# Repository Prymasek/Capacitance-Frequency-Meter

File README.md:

<div align="center">

# 🔬 ESP32-C3-Zero Capacitance & Frequency Meter

### Compact open-source capacitance and frequency meter

### Kompaktowy miernik pojemności i częstotliwości

<br>

🇵🇱 **Polski** | 🇬🇧 **English**

<br>

</div>

---

# 🇵🇱 Polski

## 📖 Opis projektu

**ESP32-C3-Zero Capacitance & Frequency Meter** to kompaktowy, otwartoźródłowy miernik pojemności oraz częstotliwości oparty na mikrokontrolerze **ESP32-C3-Zero**.

Projekt został stworzony jako niedrogie i praktyczne narzędzie pomiarowe do pracy z elektroniką. Urządzenie pozwala mierzyć pojemność kondensatorów od około **33 pF** oraz częstotliwość sygnałów cyfrowych do **250 kHz**.

Repozytorium zawiera zarówno część programową, jak i sprzętową projektu: firmware, schemat oraz projekt PCB wykonany w **KiCad 9.0**.

---

## 📸 Zdjęcia projektu

<div align="center">

### Gotowe urządzenie

<br><br>

### Spód płytki PCB

<br><br>

### Wizualizacja 3D PCB

</div>

---

## ✨ Najważniejsze funkcje

* ⚡ Pomiar pojemności kondensatorów
* 📡 Pomiar częstotliwości sygnałów
* 🔁 Automatyczny dobór zakresu pomiarowego
* 🎯 Funkcja TARE do kompensacji pojemności pasożytniczej
* ⏸️ Funkcja zatrzymania pomiaru częstotliwości
* 🧩 Projekt PCB wykonany w KiCad 9.0
* 🔓 Otwarty kod źródłowy
* 🛠️ Możliwość dalszej rozbudowy projektu

---

## ⚙️ Zasada działania

### ⚡ Pomiar pojemności

Pomiar pojemności realizowany jest poprzez pomiar czasu ładowania kondensatora przez rezystor o znanej wartości.

Mikrokontroler **ESP32-C3-Zero** mierzy czas potrzebny do osiągnięcia określonego progu napięcia wykrywanego przez szybki komparator **LT1016**.

W projekcie zastosowano dwa zakresy pomiarowe:

| Zakres          | Rezystor |
| --------------- | -------- |
| Małe pojemności | 100 kΩ   |
| Duże pojemności | 2.2 kΩ   |

Przełączanie zakresu odbywa się automatycznie w programie.

---

### 📡 Pomiar częstotliwości

Sygnał wejściowy podawany jest bezpośrednio na wejście mikrokontrolera ESP32-C3.

Każde narastające zbocze sygnału wywołuje przerwanie sprzętowe. Program zlicza impulsy w określonym czasie, a następnie przelicza wynik na częstotliwość.

Obsługiwane jednostki:

* Hz
* kHz
* MHz

---

## 🔧 Wykorzystane elementy

| Element         | Opis                       |
| --------------- | -------------------------- |
| ESP32-C3-Zero   | Główny mikrokontroler      |
| LT1016          | Szybki komparator napięcia |
| Rezystor 100 kΩ | Zakres małych pojemności   |
| Rezystor 2.2 kΩ | Zakres dużych pojemności   |
| Przyciski TACT  | Sterowanie urządzeniem     |
| Złącza goldpin  | Wejścia pomiarowe          |

---

## 📦 Zawartość repozytorium

Repozytorium zawiera:

* 📄 Firmware dla ESP32-C3-Zero
* 🧩 Schemat elektryczny KiCad 9.0
* 🧩 Projekt PCB KiCad 9.0
* 📷 Zdjęcia gotowego urządzenia
* 📘 Dokumentację projektu

---

## 📂 Struktura projektu

```text
.
├── firmware/
│   └── cap&frq_meter.ino
│
├── hardware/
│   ├── cap&frq_meter.kicad_sch
│   └── cap&frq_meter.kicad_pcb
│
├── images/
│
├── README.md
└── LICENSE
```

---

## 🛠️ Oprogramowanie

Firmware został napisany w języku **C++** z wykorzystaniem środowiska **Arduino IDE** oraz rdzenia **Arduino Core for ESP32**.

Wykorzystane biblioteki:

* Arduino Core for ESP32
* LiquidCrystal

---

## 🚀 Możliwe rozszerzenia

* Pomiar ESR kondensatorów
* Pomiar rezystancji
* Pomiar indukcyjności
* Wyświetlacz OLED/TFT
* Zasilanie akumulatorowe
* Automatyczna kalibracja
* Rozszerzenie zakresów pomiarowych

---

<br>

<div align="center">

# 🇬🇧 English

</div>

---

## 📖 Project Description

**ESP32-C3-Zero Capacitance & Frequency Meter** is a compact open-source capacitance and frequency meter based on the **ESP32-C3-Zero** microcontroller.

The project was created as a low-cost and practical measurement tool for electronics work. The device can measure capacitor values starting from approximately **33 pF** and digital signal frequencies up to **250 kHz**.

This repository contains both the software and hardware parts of the project: firmware, schematic and PCB design created in **KiCad 9.0**.

---

## 📸 Project Gallery

<div align="center">

### Finished Device

<br><br>

### PCB Bottom Layer

<br><br>

### 3D PCB View

</div>

---

## ✨ Key Features

* ⚡ Capacitance measurement
* 📡 Frequency measurement
* 🔁 Automatic measurement range selection
* 🎯 TARE compensation for parasitic capacitance
* ⏸️ Frequency measurement hold function
* 🧩 PCB design created in KiCad 9.0
* 🔓 Open-source firmware
* 🛠️ Easy to modify and expand

---

## ⚙️ Operating Principle

### ⚡ Capacitance Measurement

Capacitance is measured by monitoring the charging time of a capacitor through a resistor with a known value.

The **ESP32-C3-Zero** measures the time required to reach a voltage threshold detected by the high-speed **LT1016** comparator.

Two measurement ranges are used:

| Range              | Resistor |
| ------------------ | -------- |
| Small capacitances | 100 kΩ   |
| Large capacitances | 2.2 kΩ   |

Range switching is performed automatically in firmware.

---

### 📡 Frequency Measurement

The input signal is connected directly to an ESP32-C3 input pin.

Each rising edge of the signal generates a hardware interrupt. The firmware counts pulses over a defined time period and converts the result into frequency.

Supported units:

* Hz
* kHz
* MHz

---

## 🔧 Hardware Components

| Component       | Description                   |
| --------------- | ----------------------------- |
| ESP32-C3-Zero   | Main microcontroller          |
| LT1016          | High-speed voltage comparator |
| 100 kΩ resistor | Small capacitance range       |
| 2.2 kΩ resistor | Large capacitance range       |
| TACT switches   | User controls                 |
| Pin headers     | Measurement inputs            |

---

## 📦 Repository Contents

This repository contains:

* 📄 Firmware for ESP32-C3-Zero
* 🧩 KiCad 9.0 schematic file
* 🧩 KiCad 9.0 PCB file
* 📷 Photos of the assembled device
* 📘 Project documentation

---

## 📂 Project Structure

```text
.
├── firmware/
│   └── cap&frq_meter.ino
│
├── hardware/
│   ├── cap&frq_meter.kicad_sch
│   └── cap&frq_meter.kicad_pcb
│
├── images/
│
├── README.md
└── LICENSE
```

---

## 🛠️ Software

The firmware is written in **C++** using **Arduino IDE** and **Arduino Core for ESP32**.

Libraries used:

* Arduino Core for ESP32
* LiquidCrystal

---

## 🚀 Future Improvements

* ESR measurement
* Resistance measurement
* Inductance measurement
* OLED/TFT display support
* Battery-powered version
* Automatic calibration
* Extended measurement ranges

---

## 📄 License

Released under the MIT License.

Feel free to use, modify and improve the project.

---

<div align="center">

### ⭐ If you like this project, consider leaving a star on GitHub.

</div>

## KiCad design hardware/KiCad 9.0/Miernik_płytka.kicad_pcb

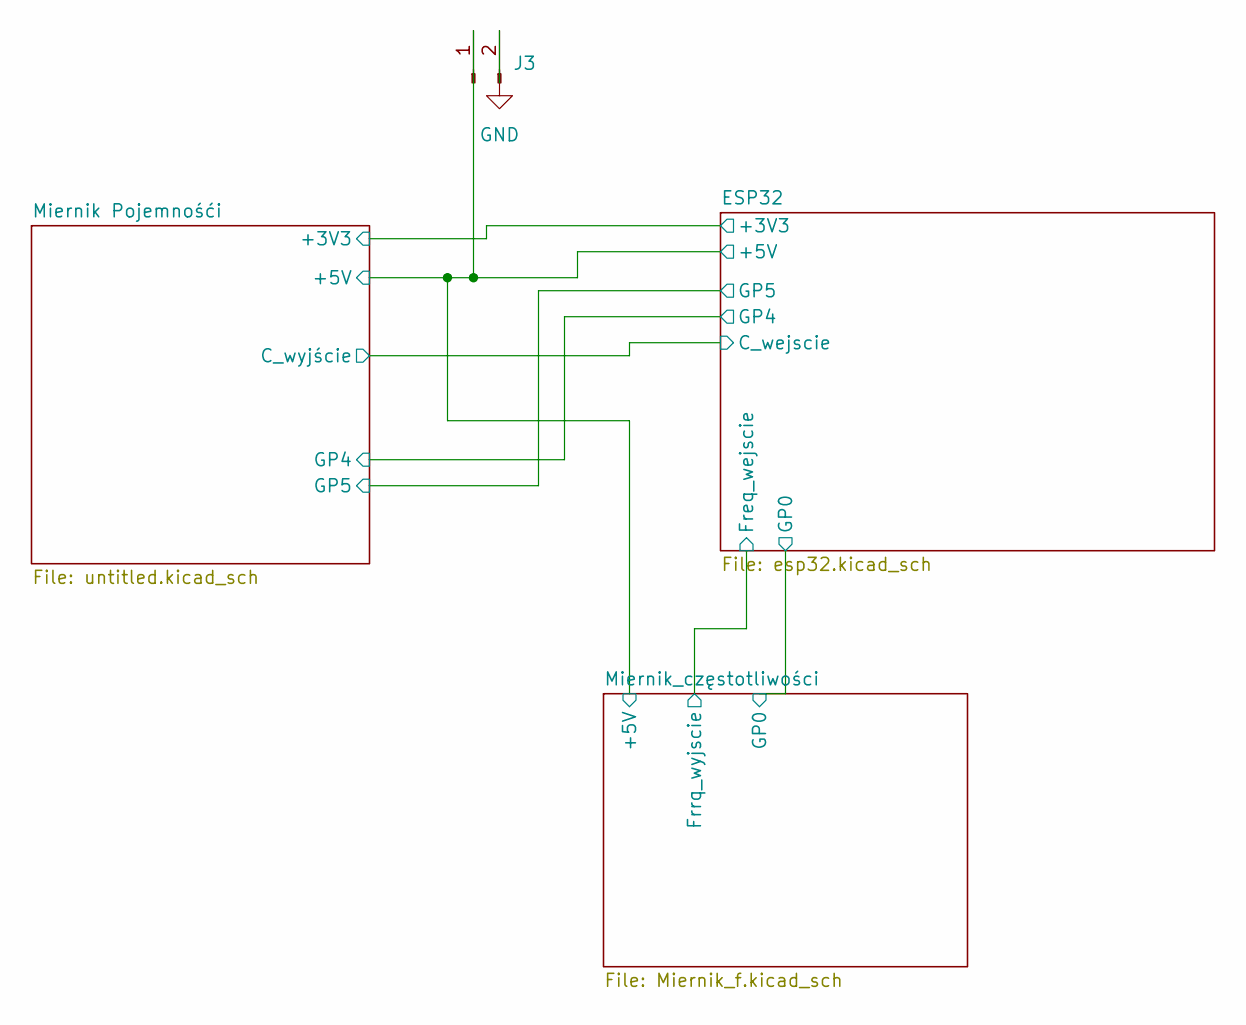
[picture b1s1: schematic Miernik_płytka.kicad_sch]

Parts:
J3: Conn_01x02_Pin; PinSocket_1x02_P2.54mm_Vertical

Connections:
/ESP32/+5V: J3.1; also elsewhere on the board
GND: J3.2; also elsewhere on the board

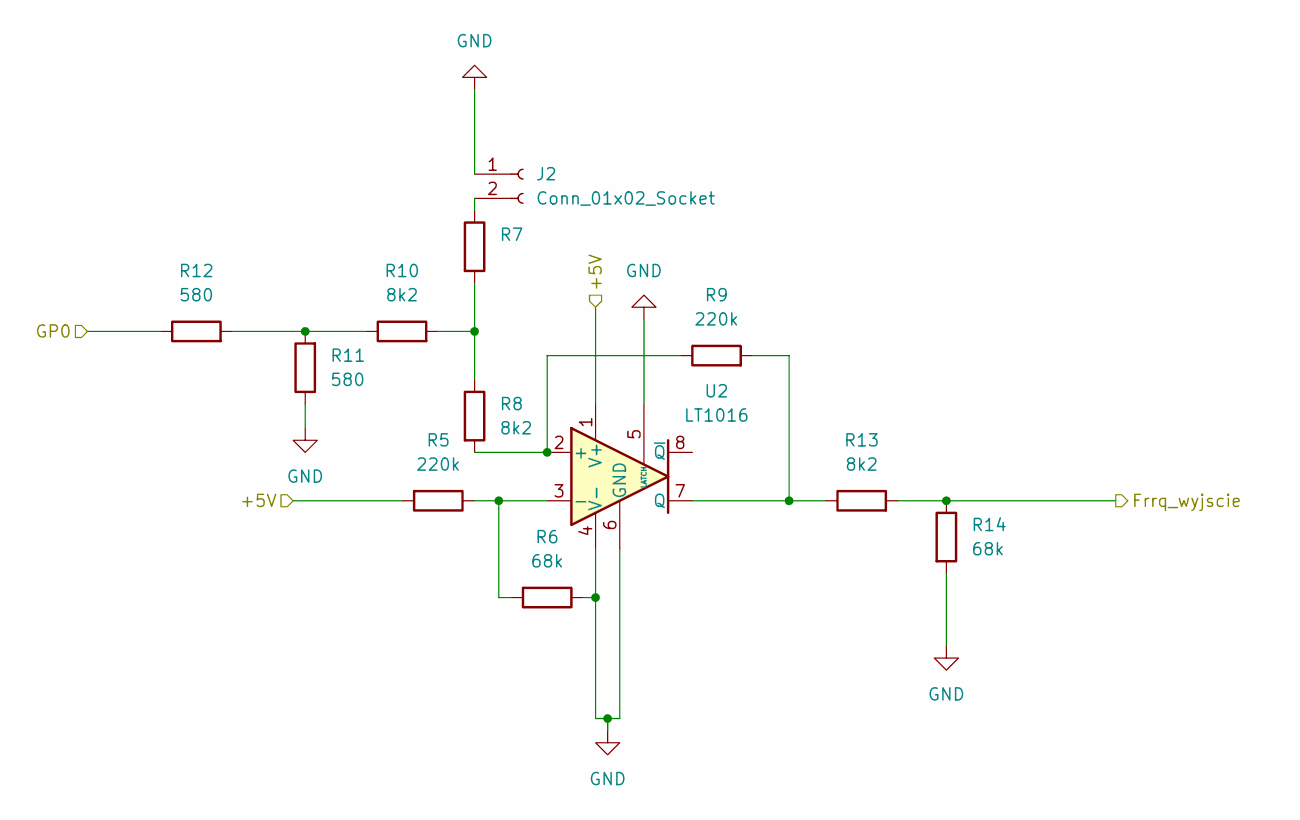
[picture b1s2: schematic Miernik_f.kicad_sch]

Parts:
J2: Conn_01x02_Socket; PinSocket_1x02_P2.54mm_Vertical
R5, R9: 220k; R_0603_1608Metric_Pad0.98x0.95mm_HandSolder
R6, R14: 68k; R_0603_1608Metric_Pad0.98x0.95mm_HandSolder
R7, R8, R10, R13: 8k2; R_0603_1608Metric_Pad0.98x0.95mm_HandSolder
R11, R12: 580; R_0603_1608Metric_Pad0.98x0.95mm_HandSolder
U2: LT1016; DIP-8_W7.62mm

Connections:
/ESP32/+5V: R5.2, U2.1 (V+); also elsewhere on the board
/ESP32/Freq_wejscie: R13.2, R14.1; also elsewhere on the board
/ESP32/GP0: R12.1; also elsewhere on the board
GND: J2.1, R6.1, R11.1, R14.2, U2.4 (V-), U2.5 (LATCH), U2.6 (GND); also elsewhere on the board
unnamed: J2.2, R7.1
unnamed: R10.1, R11.2, R12.2
unnamed: R7.2, R8.1, R10.2
unnamed: R8.2, R9.1, U2.2 (+)
unnamed: R5.1, R6.2, U2.3 (-)
unnamed: R9.2, R13.1, U2.7 (Q)

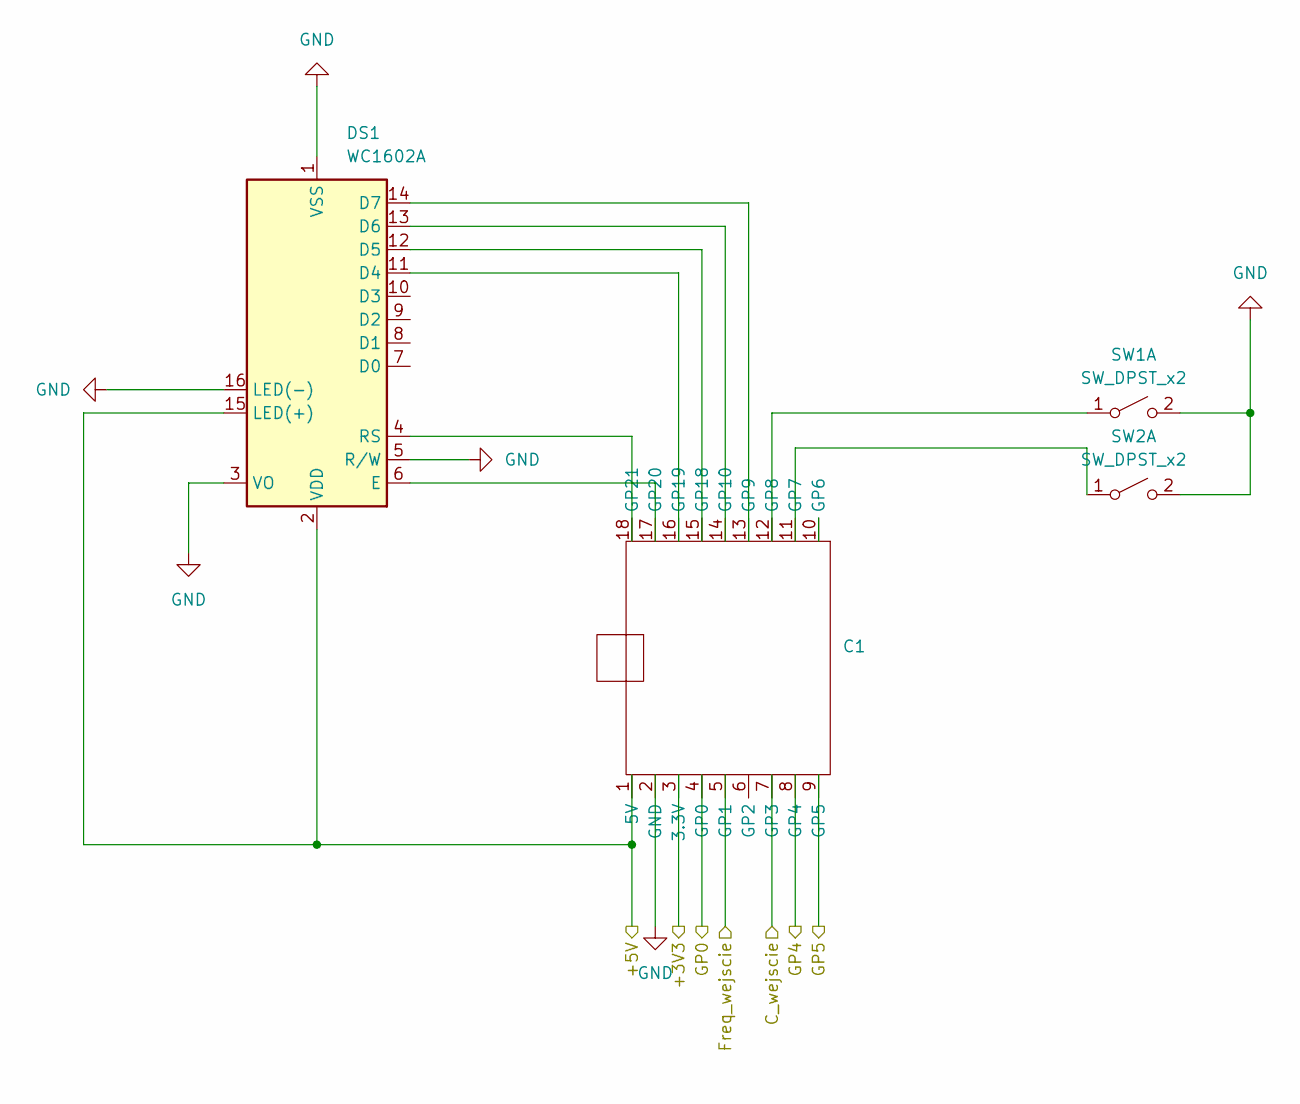
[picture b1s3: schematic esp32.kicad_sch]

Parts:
C1: ESP32_C3_ZERO
DS1: WC1602A
SW1, SW2: SW_DPST_x2; SW_PUSH_6mm_H4.3mm

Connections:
/ESP32/+3V3: C1.3 (3.3V); also elsewhere on the board
/ESP32/+5V: C1.1 (5V), DS1.2 (VDD), DS1.15 (LED(+)); also elsewhere on the board
/ESP32/C_wejscie: C1.7 (GP3); also elsewhere on the board
/ESP32/Freq_wejscie: C1.5 (GP1); also elsewhere on the board
/ESP32/GP0: C1.4 (GP0); also elsewhere on the board
/ESP32/GP4: C1.8 (GP4); also elsewhere on the board
/ESP32/GP5: C1.9 (GP5); also elsewhere on the board
GND: C1.2 (GND), DS1.1 (VSS), DS1.3 (VO), DS1.5 (R/W), DS1.16 (LED(-)), SW1.2 (B), SW2.2 (B); also elsewhere on the board
unnamed: C1.11 (GP7), SW2.1 (A)
unnamed: C1.12 (GP8), SW1.1 (A)
unnamed: C1.13 (GP9), DS1.14 (D7)
unnamed: C1.14 (GP10), DS1.13 (D6)
unnamed: C1.15 (GP18), DS1.12 (D5)
unnamed: C1.16 (GP19), DS1.11 (D4)
unnamed: C1.17 (GP20), DS1.6 (E)
unnamed: C1.18 (GP21), DS1.4 (RS)

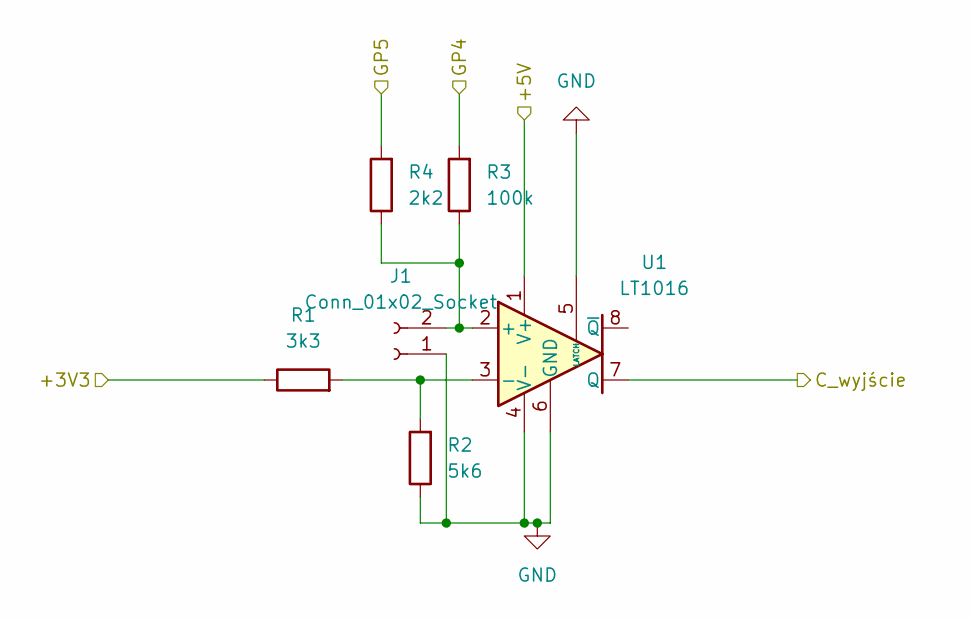
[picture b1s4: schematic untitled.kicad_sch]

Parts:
J1: Conn_01x02_Socket; PinSocket_1x02_P2.54mm_Vertical
R1: 3k3; R_0603_1608Metric_Pad0.98x0.95mm_HandSolder
R2: 5k6; R_0603_1608Metric_Pad0.98x0.95mm_HandSolder
R3: 100k; R_0603_1608Metric_Pad0.98x0.95mm_HandSolder
R4: 2k2; R_0603_1608Metric_Pad0.98x0.95mm_HandSolder
U1: LT1016; DIP-8_W7.62mm

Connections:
/ESP32/+3V3: R1.1; also elsewhere on the board
/ESP32/+5V: U1.1 (V+); also elsewhere on the board
/ESP32/C_wejscie: U1.7 (Q); also elsewhere on the board
/ESP32/GP4: R3.2; also elsewhere on the board
/ESP32/GP5: R4.2; also elsewhere on the board
GND: J1.1, R2.1, U1.4 (V-), U1.5 (LATCH), U1.6 (GND); also elsewhere on the board
unnamed: J1.2, R3.1, R4.1, U1.2 (+)
unnamed: R1.2, R2.2, U1.3 (-)

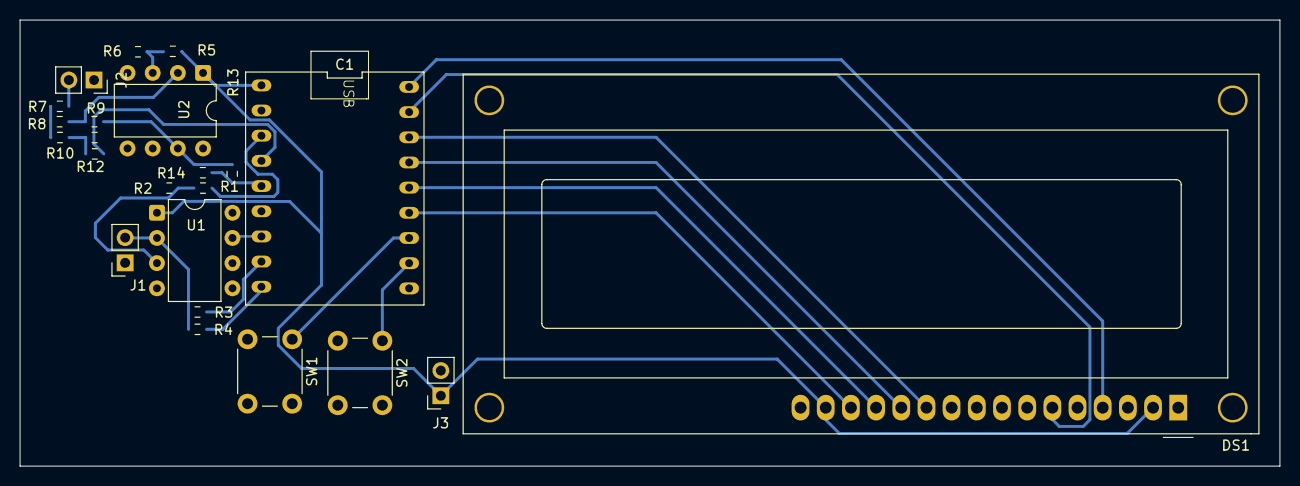
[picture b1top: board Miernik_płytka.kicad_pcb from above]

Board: 2 copper layers, 127.1 x 45.0 mm, 23 parts (0 on the bottom side), 24 nets.

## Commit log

2026-06-08 sas
    sads fajne
2026-06-08 s
    sd
